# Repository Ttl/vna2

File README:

Second version of the homemade 30 MHZ - 6 GHz single receiver VNA design files.

First version: https://github.com/Ttl/vna

For more information see: http://hforsten.com/improved-homemade-vna.html

FPGA can be programmed with Openocd (http://openocd.org/). Scripts for programming the FPGA and SPI flash are in the "openocd" folder. Copy the bit file to openocd folder and use the command "openocd -f <script.cfg>" to program the board.

Before communication is possible with the board through USB, FT2232D EEPROM needs to be programmed. Port B needs to be changed in FIFO 245 mode. This can be done using FTDIs "ft-prog" tool.

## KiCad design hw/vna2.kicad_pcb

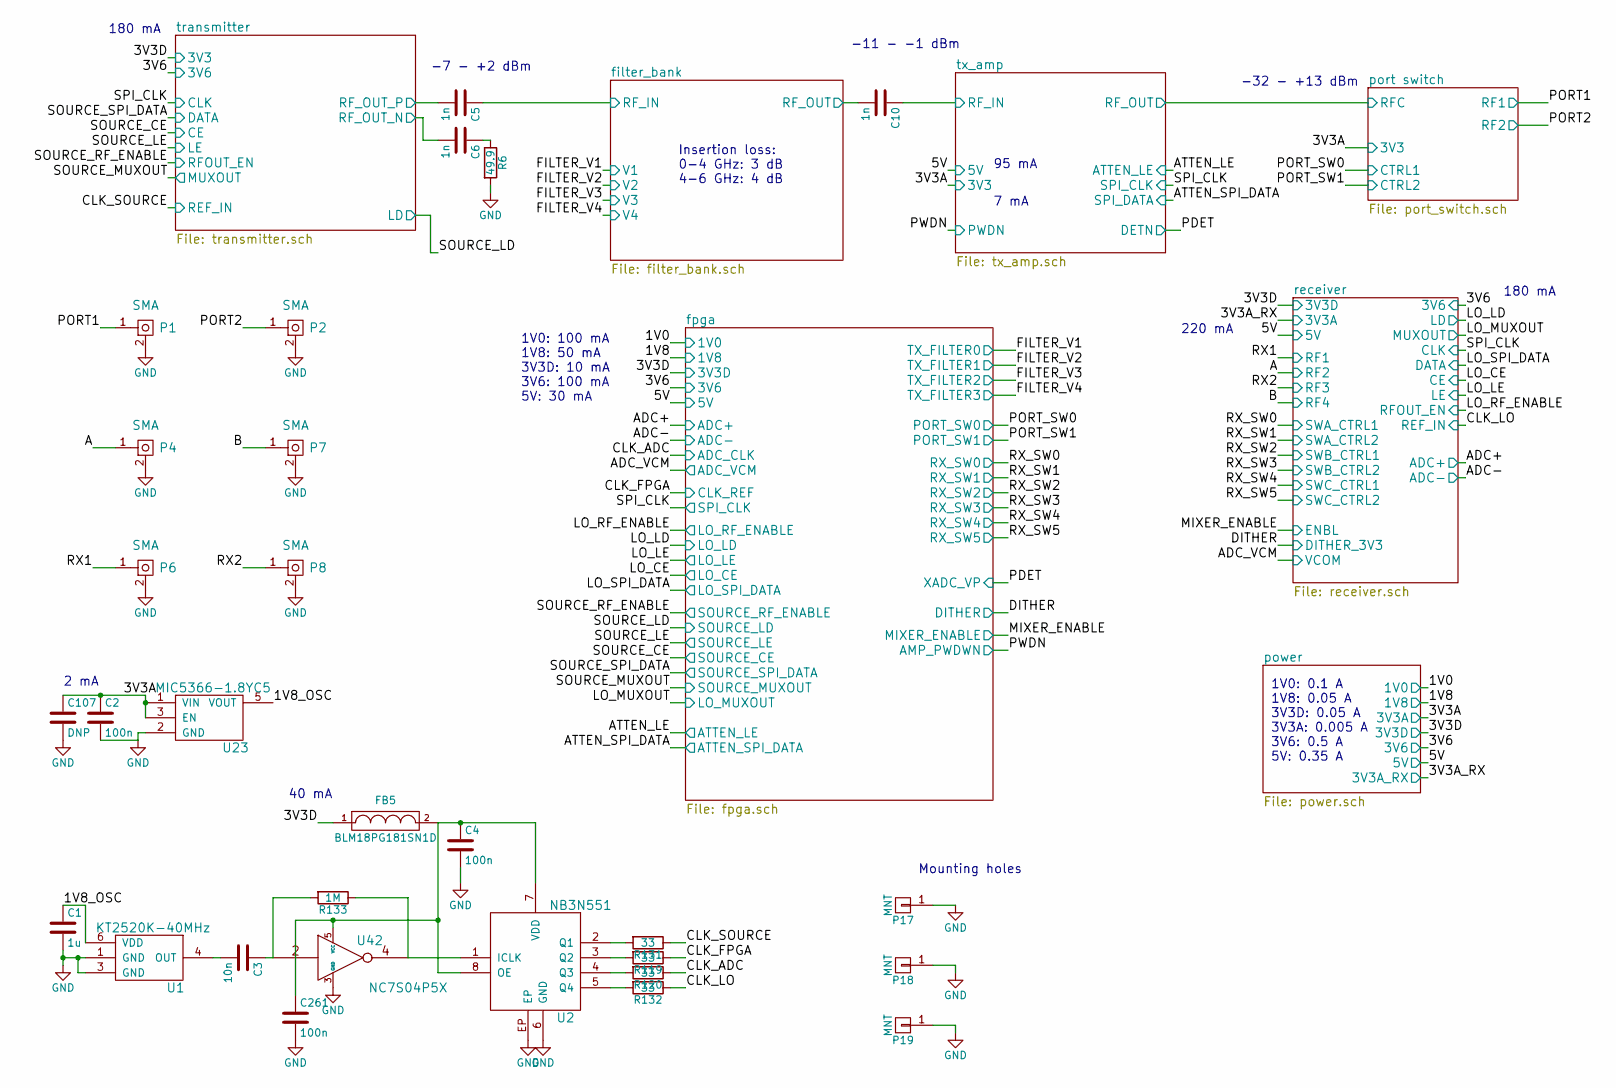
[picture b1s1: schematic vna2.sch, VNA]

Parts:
C1: 1u; C_0402b
C2, C4, C261: 100n; C_0402b
C3: 10n; C_0402b
C5, C6, C10: 1n; C_0402b
C107: DNP; C_0805b
FB5: BLM18PG181SN1D; C_0603b
P1, P2, P4, P6, P7, P8: SMA; CONSMA003.062
P17, P18, P19: MNT; MountingHole_3.2mm_M3_Pad_Via_mod
R6: 49.9; R_0402b
R119, R120, R131, R132: 33; R_0402b
R133: 1M; R_0402b
U1: KT2520K-40MHz; KT2520K
U2: NB3N551; DFN-8
U23: MIC5366-1.8YC5; SOT-353
U42: NC7S04P5X; SOT-353

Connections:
/1V8_OSC: C1.1, U1.6 (VDD), U23.5 (VOUT)
/3V3A: C2.1, C107.1, U23.1 (VIN), U23.3 (EN); also elsewhere on the board
/3V3D: FB5.1; also elsewhere on the board
/A: P4.1; also elsewhere on the board
/B: P7.1; also elsewhere on the board
/CLK_ADC: R120.1; also elsewhere on the board
/CLK_FPGA: R119.1; also elsewhere on the board
/CLK_LO: R132.1; also elsewhere on the board
/CLK_SOURCE: R131.1; also elsewhere on the board
/PORT1: P1.1; also elsewhere on the board
/PORT2: P2.1; also elsewhere on the board
/RX1: P6.1; also elsewhere on the board
/RX2: P8.1; also elsewhere on the board
/filter_bank/RF_IN: C5.1; also elsewhere on the board
/filter_bank/RF_OUT: C10.2; also elsewhere on the board
/transmitter/RF_OUT_N: C6.2; also elsewhere on the board
/transmitter/RF_OUT_P: C5.2; also elsewhere on the board
/tx_amp/RF_IN: C10.1; also elsewhere on the board
GND: C1.2, C2.2, C4.2, C107.2, C261.2, P1.2, P2.2, P4.2, P6.2, P7.2, P8.2, P17.1, P18.1, P19.1, R6.2, U1.1 (GND), U1.3 (GND), U2.6 (GND), U2.EP, U23.2 (GND), U42.3 (GND); also elsewhere on the board
unnamed: C3.1, R133.2, U42.2
unnamed: C3.2, U1.4 (OUT)
unnamed: C6.1, R6.1
unnamed: C4.1, C261.1, FB5.2, U2.7 (VDD), U2.8 (OE), U42.5 (VCC)
unnamed: R119.2, U2.3 (Q2)
unnamed: R120.2, U2.4 (Q3)
unnamed: R131.2, U2.2 (Q1)
unnamed: R132.2, U2.5 (Q4)
unnamed: R133.1, U2.1 (ICLK), U42.4

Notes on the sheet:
2 mA
Insertion loss: 0-4 GHz: 3 dB 4-6 GHz: 4 dB
-7 - +2 dBm
-11 - -1 dBm
-32 - +13 dBm
180 mA
220 mA
95 mA
7 mA
1V0: 100 mA 1V8: 50 mA 3V3D: 10 mA 3V6: 100 mA 5V: 30 mA
1V0: 0.1 A 1V8: 0.05 A 3V3D: 0.05 A 3V3A: 0.005 A 3V6: 0.5 A 5V: 0.35 A
Mounting holes
40 mA

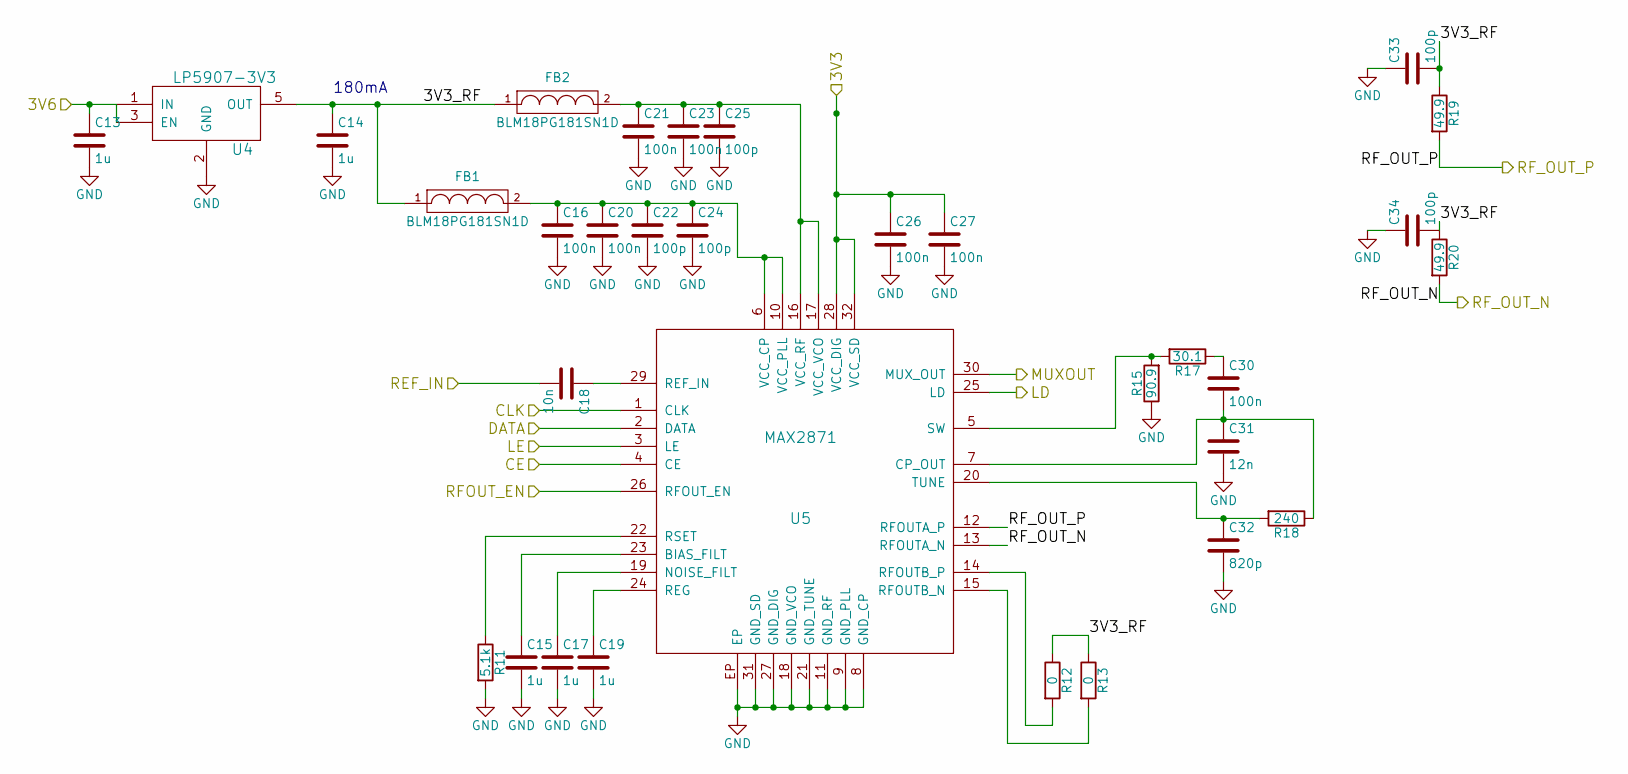
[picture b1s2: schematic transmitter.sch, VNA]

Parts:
C13, C14, C15, C17, C19: 1u; C_0603b
C16, C20, C21, C23, C26, C27, C30: 100n; C_0402b
C18: 10n; C_0402b
C22, C24, C25, C33, C34: 100p; C_0402b
C31: 12n; C_0402b
C32: 820p; C_0402b
FB1, FB2: BLM18PG181SN1D; C_0603b
R11: 5.1k; R_0402b
R12, R13: 0; R_0402b
R15: 90.9; R_0402b
R17: 30.1; R_0402b
R18: 240; R_0402b
R19, R20: 49.9; R_0402b
U4: LP5907-3V3; SOT-23-5
U5: MAX2871; TQFN-32

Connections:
/3V3D: C26.1, C27.1, U5.28 (VCC_DIG), U5.32 (VCC_SD); also elsewhere on the board
/3V6: C13.1, U4.1 (IN), U4.3 (EN); also elsewhere on the board
/CLK_SOURCE: C18.2; also elsewhere on the board
/SOURCE_CE: U5.4 (CE); also elsewhere on the board
/SOURCE_LD: U5.25 (LD); also elsewhere on the board
/SOURCE_LE: U5.3 (LE); also elsewhere on the board
/SOURCE_MUXOUT: U5.30 (MUX_OUT); also elsewhere on the board
/SOURCE_RF_ENABLE: U5.26 (RFOUT_EN); also elsewhere on the board
/SOURCE_SPI_DATA: U5.2 (DATA); also elsewhere on the board
/SPI_CLK: U5.1 (CLK); also elsewhere on the board
/transmitter/3V3_RF: C14.1, C33.2, C34.2, FB1.1, FB2.1, R12.1, R13.1, R19.1, R20.1, U4.5 (OUT)
/transmitter/RF_OUT_N: R20.2, U5.13 (RFOUTA_N); also elsewhere on the board
/transmitter/RF_OUT_P: R19.2, U5.12 (RFOUTA_P); also elsewhere on the board
GND: C13.2, C14.2, C15.2, C16.2, C17.2, C19.2, C20.2, C21.2, C22.2, C23.2, C24.2, C25.2, C26.2, C27.2, C31.2, C32.2, C33.1, C34.1, R11.2, R15.1, U4.2 (GND), U5.8 (GND_CP), U5.9 (GND_PLL), U5.11 (GND_RF), U5.18 (GND_VCO), U5.21 (GND_TUNE), U5.27 (GND_DIG), U5.31 (GND_SD), U5.EP; also elsewhere on the board
unnamed: C15.1, U5.23 (BIAS_FILT)
unnamed: C16.1, C20.1, C22.1, C24.1, FB1.2, U5.6 (VCC_CP), U5.10 (VCC_PLL)
unnamed: C17.1, U5.19 (NOISE_FILT)
unnamed: C18.1, U5.29 (REF_IN)
unnamed: C19.1, U5.24 (REG)
unnamed: C21.1, C23.1, C25.1, FB2.2, U5.16 (VCC_RF), U5.17 (VCC_VCO)
unnamed: C30.1, R17.1
unnamed: C30.2, C31.1, R18.1, U5.7 (CP_OUT)
unnamed: C32.1, R18.2, U5.20 (TUNE)
unnamed: R11.1, U5.22 (RSET)
unnamed: R12.2, U5.14 (RFOUTB_P)
unnamed: R13.2, U5.15 (RFOUTB_N)
unnamed: R15.2, R17.2, U5.5 (SW)

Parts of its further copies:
C55, C56, C57, C59, C61: 1u; C_0603b
C58, C62, C63, C65, C68, C69, C72: 100n; C_0402b
C60: 10n; C_0402b
C64, C66, C67, C75, C76: 100p; C_0402b
C73: 12n; C_0402b
C74: 820p; C_0402b
FB3, FB4: BLM18PG181SN1D; C_0603b
R29: 5.1k; R_0402b
R30, R31: 0; R_0402b
R33: 90.9; R_0402b
R35: 30.1; R_0402b
R36: 240; R_0402b
R37, R38: 49.9; R_0402b
U8: LP5907-3V3; SOT-23-5
U9: MAX2871; TQFN-32

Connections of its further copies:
/3V3D: C68.1, C69.1, U9.28 (VCC_DIG), U9.32 (VCC_SD); also elsewhere on the board
/3V6: C55.1, U8.1 (IN), U8.3 (EN); also elsewhere on the board
/CLK_LO: C60.2; also elsewhere on the board
/LO_CE: U9.4 (CE); also elsewhere on the board
/LO_LD: U9.25 (LD); also elsewhere on the board
/LO_LE: U9.3 (LE); also elsewhere on the board
/LO_MUXOUT: U9.30 (MUX_OUT); also elsewhere on the board
/LO_RF_ENABLE: U9.26 (RFOUT_EN); also elsewhere on the board
/LO_SPI_DATA: U9.2 (DATA); also elsewhere on the board
/SPI_CLK: U9.1 (CLK); also elsewhere on the board
/receiver/LON: R38.2, U9.13 (RFOUTA_N); also elsewhere on the board
/receiver/LOP: R37.2, U9.12 (RFOUTA_P); also elsewhere on the board
/receiver/lo_synth/3V3_RF: C56.1, C75.2, C76.2, FB3.1, FB4.1, R30.1, R31.1, R37.1, R38.1, U8.5 (OUT)
GND: C55.2, C56.2, C57.2, C58.2, C59.2, C61.2, C62.2, C63.2, C64.2, C65.2, C66.2, C67.2, C68.2, C69.2, C73.2, C74.2, C75.1, C76.1, R29.2, R33.1, U8.2 (GND), U9.8 (GND_CP), U9.9 (GND_PLL), U9.11 (GND_RF), U9.18 (GND_VCO), U9.21 (GND_TUNE), U9.27 (GND_DIG), U9.31 (GND_SD), U9.EP; also elsewhere on the board
unnamed: C57.1, U9.23 (BIAS_FILT)
unnamed: C58.1, C62.1, C64.1, C66.1, FB3.2, U9.6 (VCC_CP), U9.10 (VCC_PLL)
unnamed: C59.1, U9.19 (NOISE_FILT)
unnamed: C60.1, U9.29 (REF_IN)
unnamed: C61.1, U9.24 (REG)
unnamed: C63.1, C65.1, C67.1, FB4.2, U9.16 (VCC_RF), U9.17 (VCC_VCO)
unnamed: C72.1, R35.1
unnamed: C72.2, C73.1, R36.1, U9.7 (CP_OUT)
unnamed: C74.1, R36.2, U9.20 (TUNE)
unnamed: R29.1, U9.22 (RSET)
unnamed: R30.2, U9.14 (RFOUTB_P)
unnamed: R31.2, U9.15 (RFOUTB_N)
unnamed: R33.2, R35.2, U9.5 (SW)

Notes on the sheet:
180mA

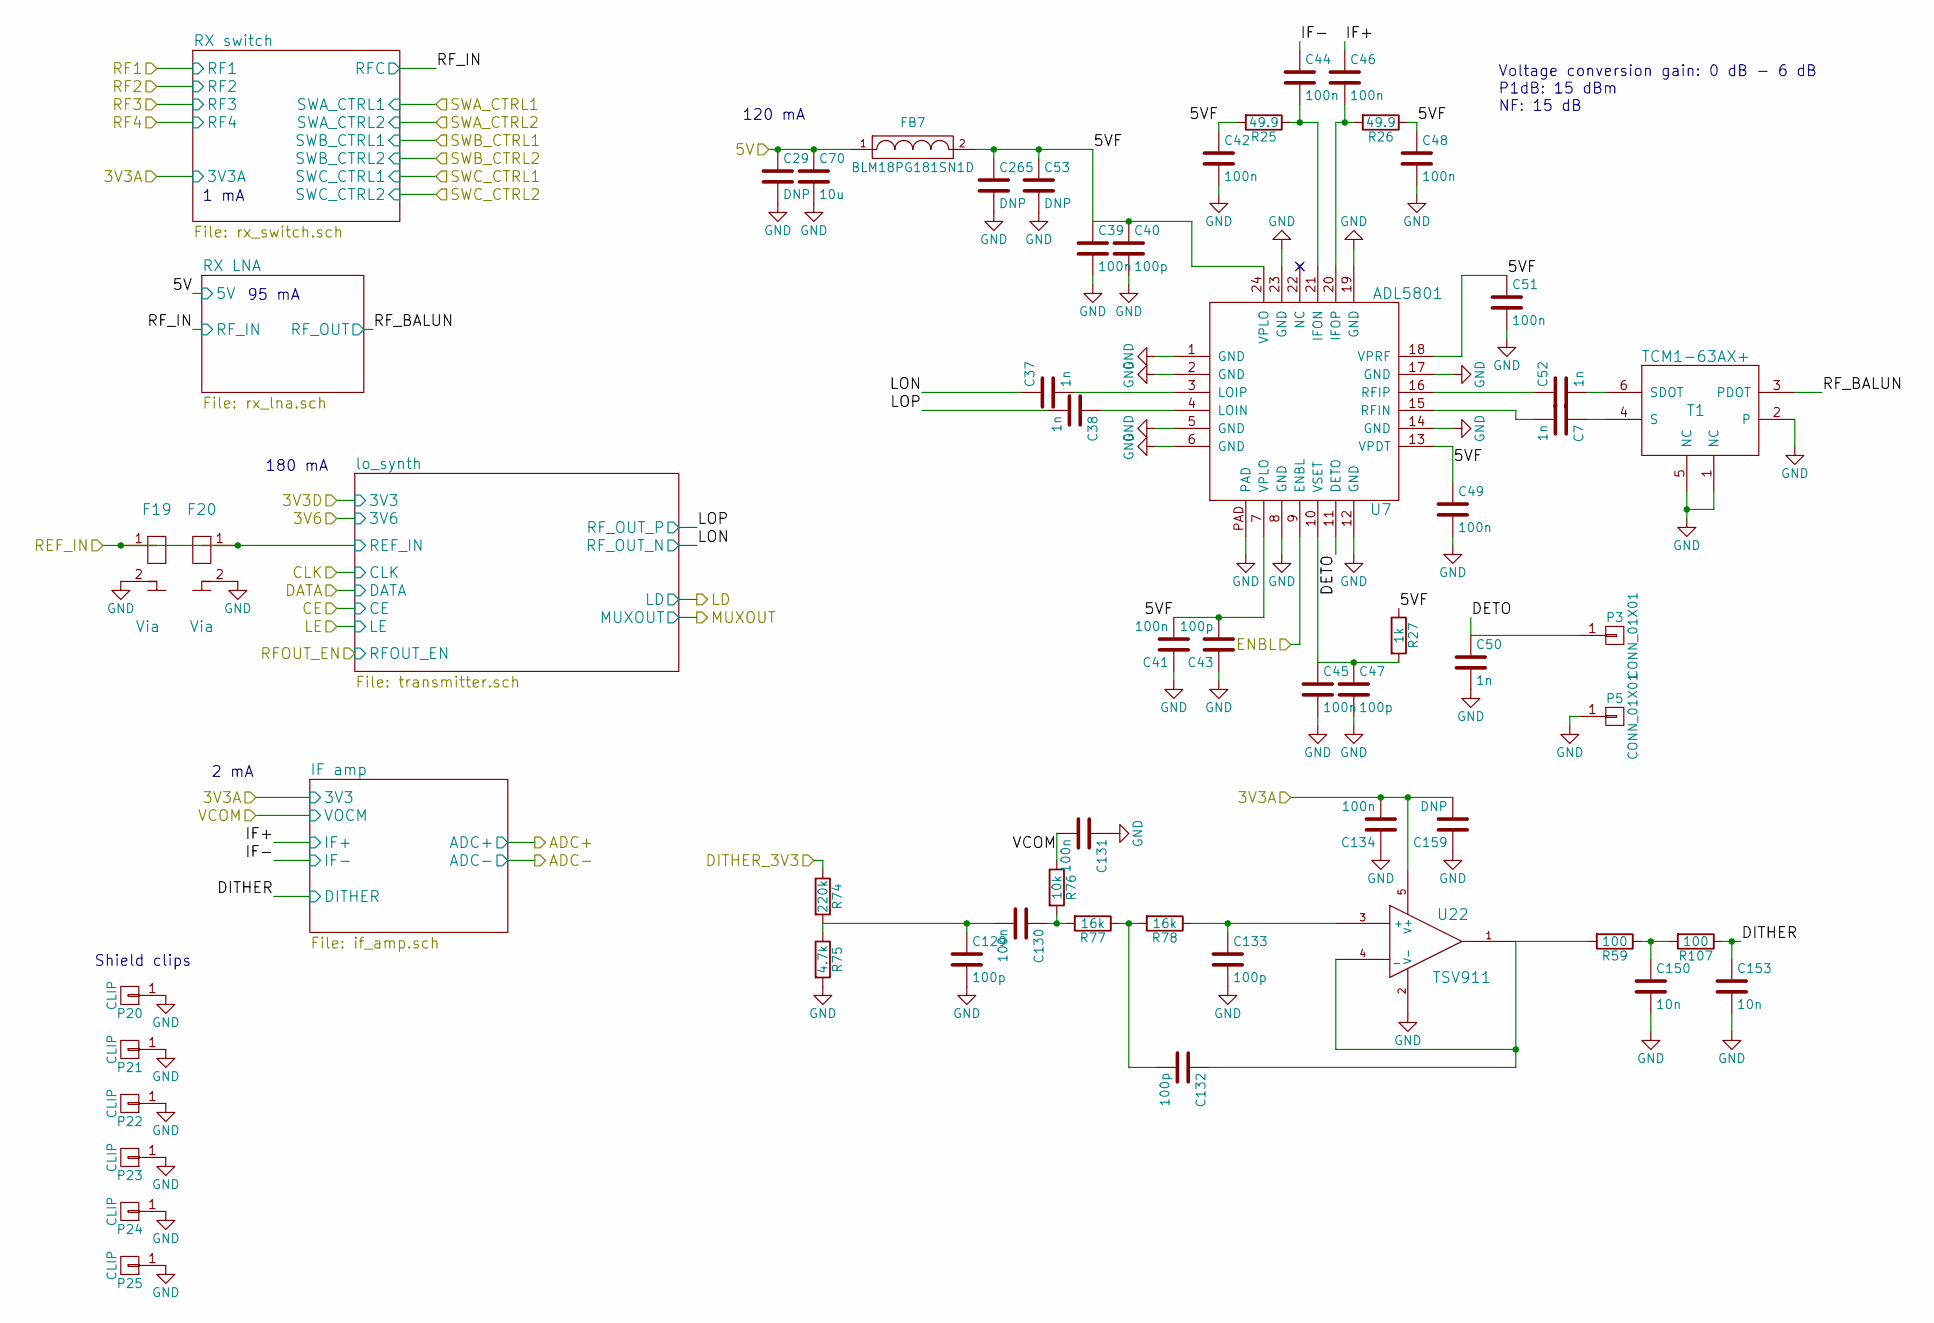
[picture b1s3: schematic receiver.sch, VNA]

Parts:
C7, C37, C38, C50, C52: 1n; C_0402b
C29: DNP; C_0603b
C39, C41, C42, C44, C45, C46, C48, C49, C51, C130, C131, C134: 100n; C_0402b
C40, C43, C47, C129, C132, C133: 100p; C_0402b
C53, C159, C265: DNP; C_0805b
C70: 10u; C_0805b
C150, C153: 10n; C_0402b
F19, F20: Via; RF_via
FB7: BLM18PG181SN1D; C_0603b
P3, P5: CONN_01X01; TP_1.00
P20, P21, P22, P23, P24, P25: CLIP; S2711-46R
R25, R26: 49.9; R_0402b
R27: 1k; R_0402b
R59, R107: 100; R_0402b
R74: 220k; R_0402b
R75: 4.7k; R_0402b
R76: 10k; R_0402b
R77, R78: 16k; R_0402b
T1: TCM1-63AX+
U7: ADL5801; VFQFN-24
U22: TSV911; SOT-23-5

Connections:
3V3A_RX: C134.2, C159.2, U22.5 (V+); also elsewhere on the board
/5V: C29.1, C70.1, FB7.1; also elsewhere on the board
/ADC_VCM: C131.2, R76.1; also elsewhere on the board
/CLK_LO: F19.1, F20.1; also elsewhere on the board
/DITHER: R74.1; also elsewhere on the board
/MIXER_ENABLE: U7.9 (ENBL); also elsewhere on the board
/receiver/5VF: C39.1, C40.1, C41.2, C42.1, C43.2, C48.1, C49.1, C51.1, C53.1, C265.1, FB7.2, R25.2, R26.1, R27.1, U7.7 (VPLO), U7.13 (VPDT), U7.18 (VPRF), U7.24 (VPLO)
/receiver/DETO: C50.1, P3.1, U7.11 (DETO)
/receiver/DITHER: C153.1, R107.1; also elsewhere on the board
/receiver/IF+: C46.1; also elsewhere on the board
/receiver/IF-: C44.1; also elsewhere on the board
/receiver/LON: C37.1; also elsewhere on the board
/receiver/LOP: C38.2; also elsewhere on the board
/receiver/RF_BALUN: T1.3 (PDOT); also elsewhere on the board
GND: C29.2, C39.2, C40.2, C41.1, C42.2, C43.1, C45.2, C47.2, C48.2, C49.2, C50.2, C51.2, C53.2, C70.2, C129.2, C131.1, C133.2, C134.1, C150.2, C153.2, C159.1, C265.2, F19.2, F20.2, P5.1, P20.1, P21.1, P22.1, P23.1, P24.1, P25.1, R75.2, T1.1 (NC), T1.2, T1.5 (NC), U7.1 (GND), U7.2 (GND), U7.5 (GND), U7.6 (GND), U7.8 (GND), U7.12 (GND), U7.14 (GND), U7.17 (GND), U7.19 (GND), U7.23 (GND), U7.PAD, U22.2 (V-); also elsewhere on the board
unnamed: C7.1, T1.4 (S)
unnamed: C7.2, U7.15 (RFIN)
unnamed: C37.2, U7.3 (LOIP)
unnamed: C38.1, U7.4 (LOIN)
unnamed: C44.2, R25.1, U7.21 (IFON)
unnamed: C45.1, C47.1, R27.2, U7.10 (VSET)
unnamed: C46.2, R26.2, U7.20 (IFOP)
unnamed: C52.1, U7.16 (RFIP)
unnamed: C52.2, T1.6 (SDOT)
unnamed: C129.1, C130.2, R74.2, R75.1
unnamed: C130.1, R76.2, R77.2
unnamed: C132.1, R59.2, U22.1, U22.4 (_)
unnamed: C132.2, R77.1, R78.2
unnamed: C133.1, R78.1, U22.3 (+)
unnamed: C150.1, R59.1, R107.2

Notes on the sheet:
Voltage conversion gain: 0 dB - 6 dB P1dB: 15 dBm NF: 15 dB
120 mA
180 mA
2 mA
Shield clips
1 mA
95 mA

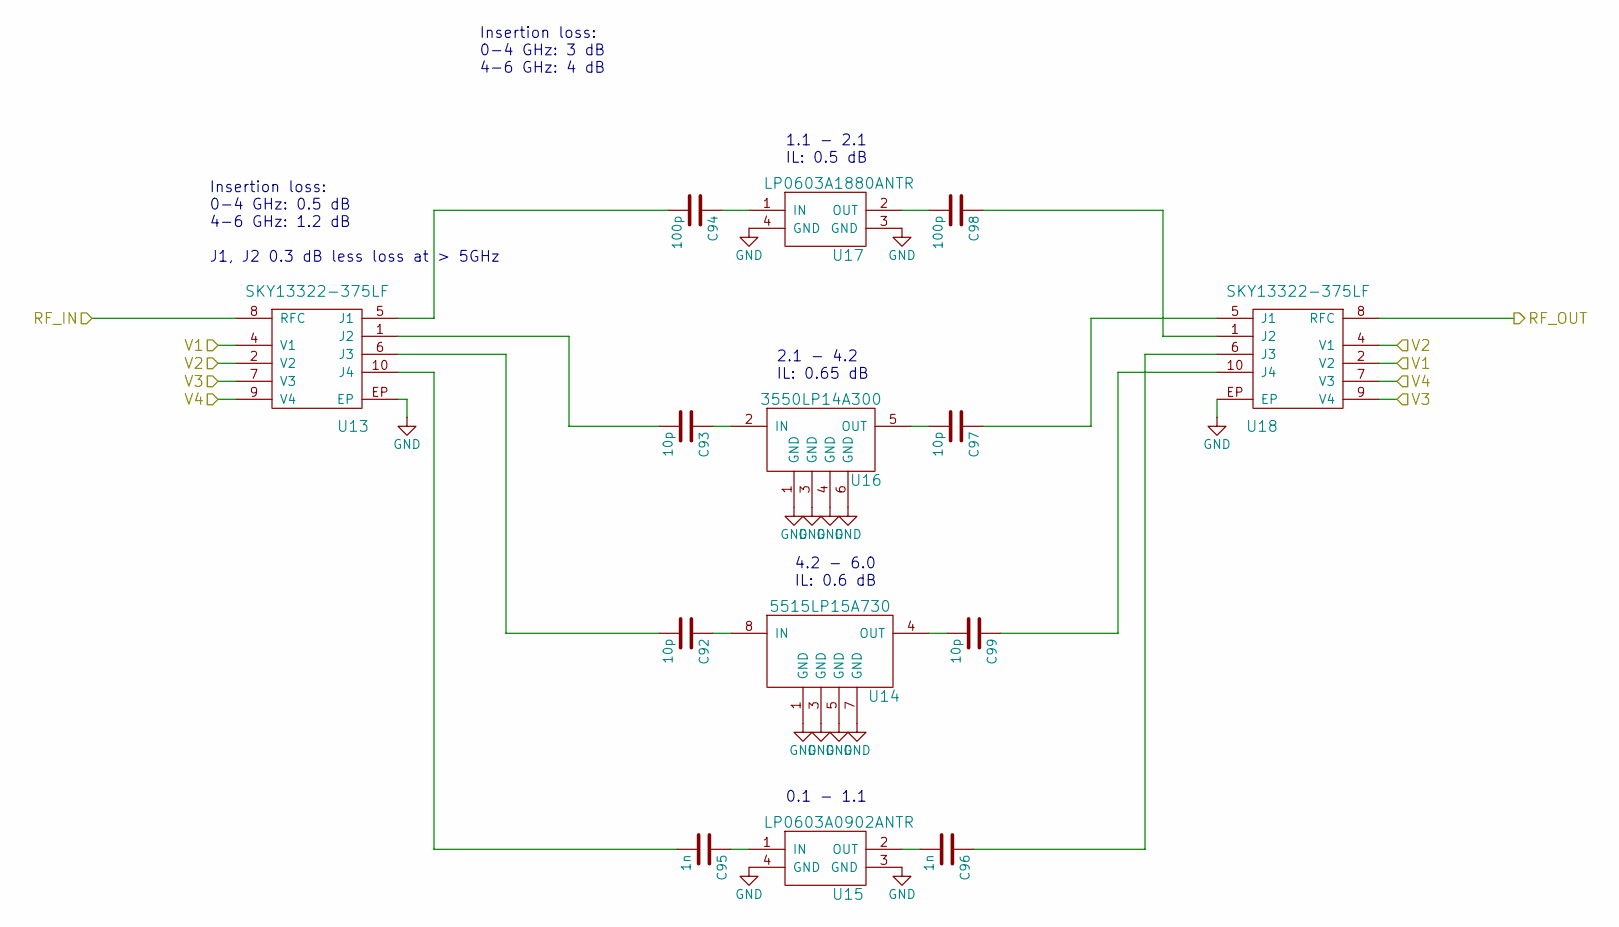
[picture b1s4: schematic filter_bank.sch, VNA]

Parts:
C92, C93, C97, C99: 10p; C_0402b
C94, C98: 100p; C_0402b
C95, C96: 1n; C_0402b
U13, U18: SKY13322-375LF; MLPD-10
U14: 5515LP15A730
U15: LP0603A0902ANTR; LP0603A0902
U16: 3550LP14A300
U17: LP0603A1880ANTR; LP0603A0902

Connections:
/FILTER_V1: U13.4 (V1), U18.2 (V2); also elsewhere on the board
/FILTER_V2: U13.2 (V2), U18.4 (V1); also elsewhere on the board
/FILTER_V3: U13.7 (V3), U18.9 (V4); also elsewhere on the board
/FILTER_V4: U13.9 (V4), U18.7 (V3); also elsewhere on the board
/filter_bank/RF_IN: U13.8 (RFC); also elsewhere on the board
/filter_bank/RF_OUT: U18.8 (RFC); also elsewhere on the board
GND: U13.EP, U14.1 (GND), U14.3 (GND), U14.5 (GND), U14.7 (GND), U15.3 (GND), U15.4 (GND), U16.1 (GND), U16.3 (GND), U16.4 (GND), U16.6 (GND), U17.3 (GND), U17.4 (GND), U18.EP; also elsewhere on the board
unnamed: C92.1, U14.8 (IN)
unnamed: C92.2, U13.6 (J3)
unnamed: C93.1, U16.2 (IN)
unnamed: C93.2, U13.1 (J2)
unnamed: C94.1, U17.1 (IN)
unnamed: C94.2, U13.5 (J1)
unnamed: C95.1, U15.1 (IN)
unnamed: C95.2, U13.10 (J4)
unnamed: C96.1, U18.6 (J3)
unnamed: C96.2, U15.2 (OUT)
unnamed: C97.1, U18.5 (J1)
unnamed: C97.2, U16.5 (OUT)
unnamed: C98.1, U18.1 (J2)
unnamed: C98.2, U17.2 (OUT)
unnamed: C99.1, U18.10 (J4)
unnamed: C99.2, U14.4 (OUT)

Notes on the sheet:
Insertion loss: 0-4 GHz: 0.5 dB 4-6 GHz: 1.2 dB J1, J2 0.3 dB less loss at > 5GHz
Insertion loss: 0-4 GHz: 3 dB 4-6 GHz: 4 dB
4.2 - 6.0 IL: 0.6 dB
2.1 - 4.2 IL: 0.65 dB
1.1 - 2.1 IL: 0.5 dB
0.1 - 1.1

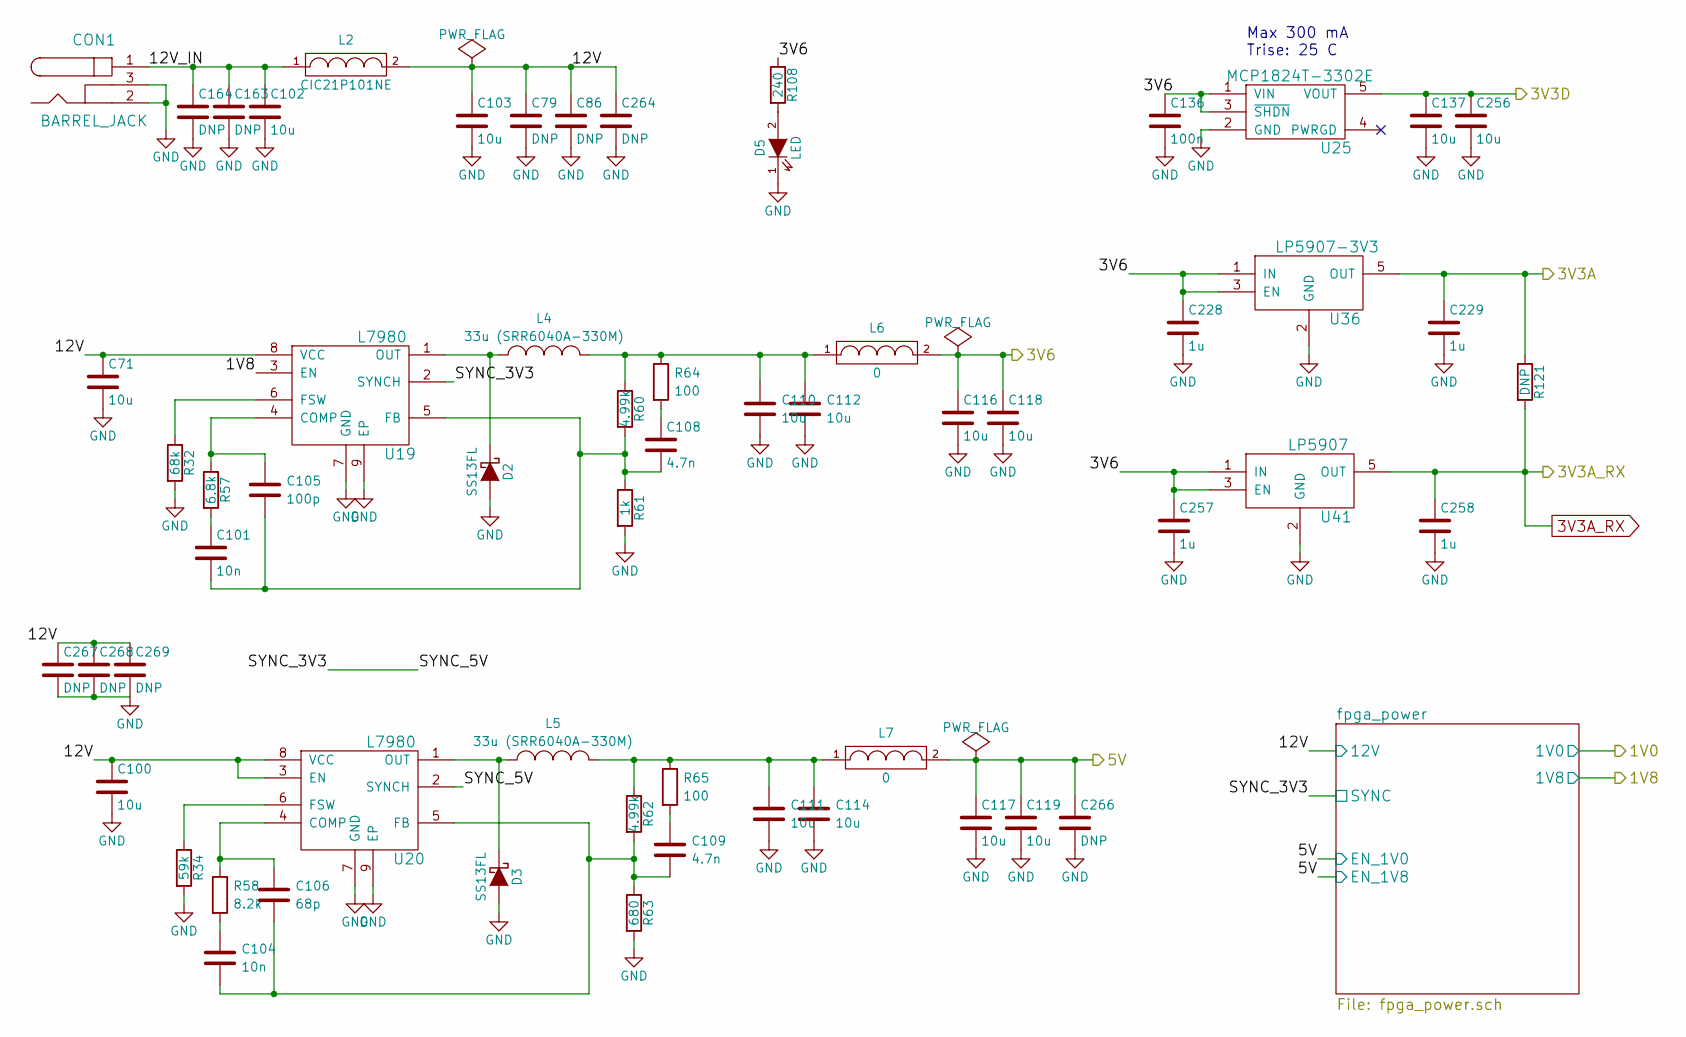
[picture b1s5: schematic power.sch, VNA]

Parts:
C71, C100, C102, C103, C110, C111, C112, C114, C116, C117, C118, C119, C137, C256: 10u; C_0805b
C79, C86, C163, C164, C264, C266, C267, C268, C269: DNP; C_0805b
C101, C104: 10n; C_0402b
C105: 100p; C_0402b
C106: 68p; C_0402b
C108, C109: 4.7n; C_0402b
C136: 100n; C_0402b
C228, C229, C257, C258: 1u; C_0603b
CON1: BARREL_JACK; EJ508A
D2, D3: SS13FL; SOD-123F
D5: LED; LED_0603
L2: CIC21P101NE; C_0805b
L4, L5: 33u (SRR6040A-330M); SRR6040A
L6, L7: 0; C_0805b
R32: 68k; R_0402b
R34: 59k; R_0402b
R57: 6.8k; R_0402b
R58: 8.2k; R_0402b
R60, R62: 4.99k; R_0402b
R61: 1k; R_0402b
R63: 680; R_0402b
R64, R65: 100; R_0402b
R108: 240; R_0402b
R121: DNP; R_0402b
U19, U20: L7980; DFN-8-1EP_3x3mm_Pitch0.5mm
U25: MCP1824T-3302E; SOT-23-5
U36: LP5907-3V3; SOT-23-5
U41: LP5907; SOT-23-5

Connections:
3V3A_RX: C258.1, R121.2, U41.5 (OUT); also elsewhere on the board
/1V8: U19.3 (EN); also elsewhere on the board
/3V3A: C229.1, R121.1, U36.5 (OUT); also elsewhere on the board
/3V3D: C137.1, C256.1, U25.5 (VOUT); also elsewhere on the board
/3V6: C116.1, C118.1, C136.1, C228.1, C257.1, L6.2, R108.1, U25.1 (VIN), U25.3 (~SHDN), U36.1 (IN), U36.3 (EN), U41.1 (IN), U41.3 (EN); also elsewhere on the board
/5V: C117.1, C119.1, C266.1, L7.2; also elsewhere on the board
/power/12V: C71.1, C79.1, C86.1, C100.1, C103.1, C264.1, C267.1, C268.1, C269.1, L2.2, U19.8 (VCC), U20.3 (EN), U20.8 (VCC); also elsewhere on the board
/power/12V_IN: C102.1, C163.1, C164.1, CON1.1, L2.1
/power/SYNC_3V3: U19.2 (SYNCH), U20.2 (SYNCH); also elsewhere on the board
GND: C71.2, C79.2, C86.2, C100.2, C102.2, C103.2, C110.2, C111.2, C112.2, C114.2, C116.2, C117.2, C118.2, C119.2, C136.2, C137.2, C163.2, C164.2, C228.2, C229.2, C256.2, C257.2, C258.2, C264.2, C266.2, C267.2, C268.2, C269.2, CON1.2, CON1.3, D2.2 (A), D3.2 (A), D5.1 (K), R32.2, R34.2, R61.2, R63.2, U19.7 (GND), U19.9 (EP), U20.7 (GND), U20.9 (EP), U25.2 (GND), U36.2 (GND), U41.2 (GND); also elsewhere on the board
unnamed: C101.1, R57.2
unnamed: C101.2, C105.2, C108.2, R60.2, R61.1, U19.5 (FB)
unnamed: C104.1, R58.2
unnamed: C104.2, C106.2, C109.2, R62.2, R63.1, U20.5 (FB)
unnamed: C105.1, R57.1, U19.4 (COMP)
unnamed: C106.1, R58.1, U20.4 (COMP)
unnamed: C108.1, R64.2
unnamed: C109.1, R65.2
unnamed: C110.1, C112.1, L4.2, L6.1, R60.1, R64.1
unnamed: C111.1, C114.1, L5.2, L7.1, R62.1, R65.1
unnamed: D2.1 (K), L4.1, U19.1 (OUT)
unnamed: D3.1 (K), L5.1, U20.1 (OUT)
unnamed: D5.2 (A), R108.2
unnamed: R32.1, U19.6 (FSW)
unnamed: R34.1, U20.6 (FSW)

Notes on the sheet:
Max 300 mA Trise: 25 C

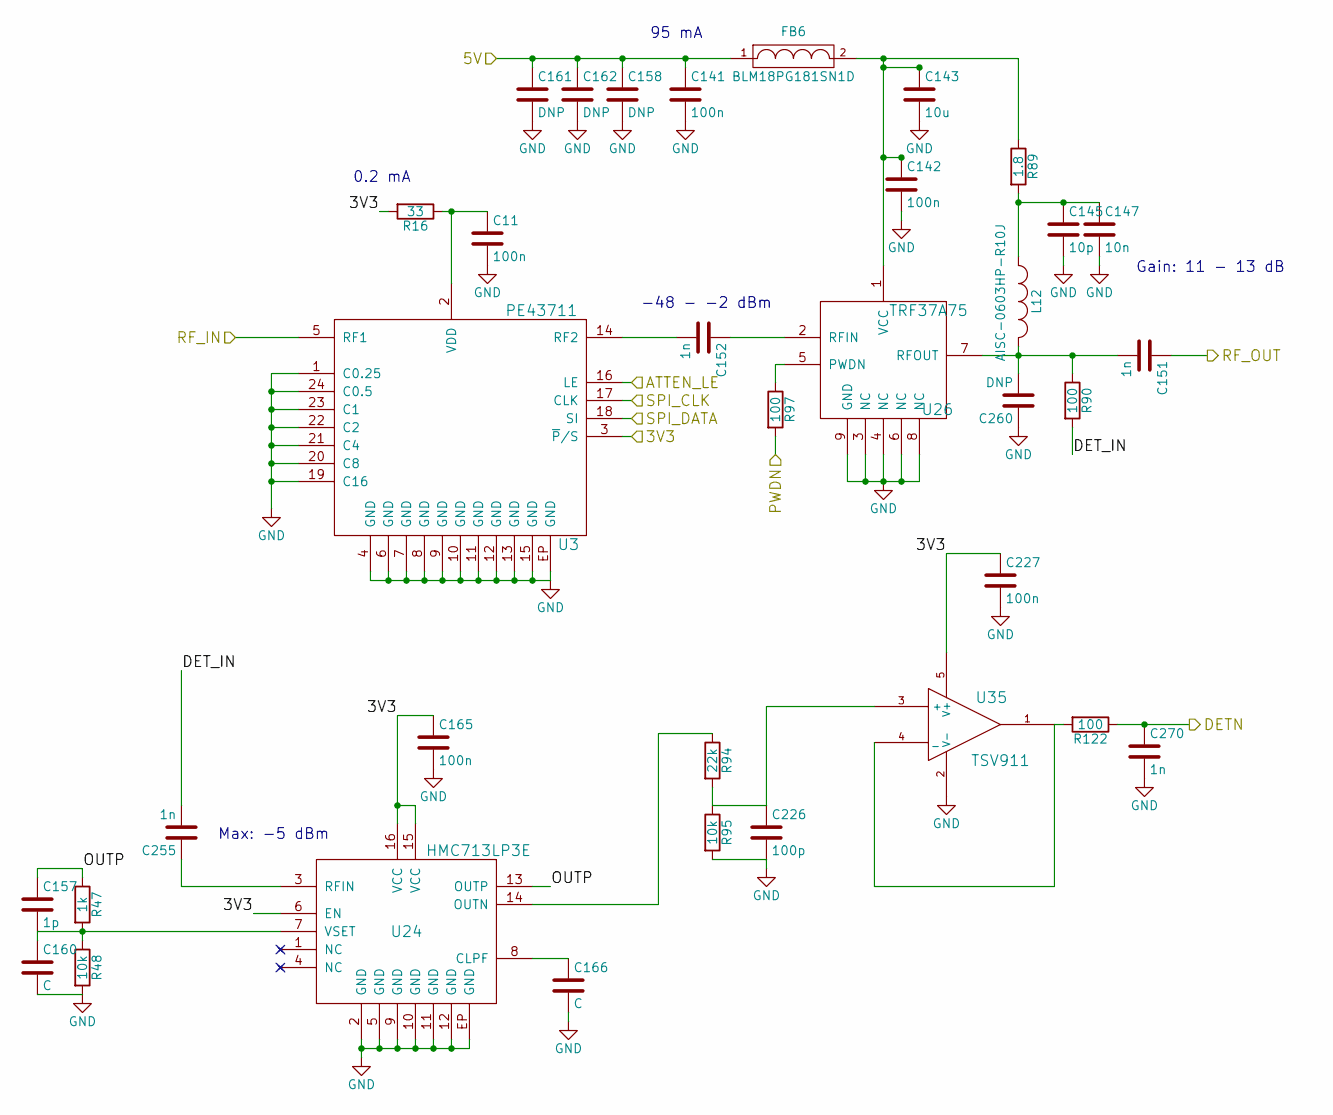
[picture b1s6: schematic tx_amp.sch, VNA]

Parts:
C11, C141, C142, C165, C227: 100n; C_0402b
C143: 10u; C_0805b
C145: 10p; C_0402b
C147: 10n; C_0402b
C151, C152, C255, C270: 1n; C_0402b
C157: 1p; C_0402b
C158: DNP; C_0805b
C160, C166: C; C_0402b
C161, C162, C260: DNP; C_0402b
C226: 100p; C_0402b
FB6: BLM18PG181SN1D; C_0603b
L12: AISC-0603HP-R10J; C_0603b
R16: 33; R_0402b
R47: 1k; R_0402b
R48, R95: 10k; R_0402b
R89: 1.8; R_0603b
R90, R97, R122: 100; R_0402b
R94: 22k; R_0402b
U3: PE43711; VQFN-24
U24: HMC713LP3E; VFQFN-16
U26: TRF37A75; DFN-8-1EP_2x2mm_Pitch0.5mm
U35: TSV911; SOT-23-5

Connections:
/3V3A: C165.1, C227.1, R16.2, U3.3 (~P~/S), U24.6 (EN), U24.15 (VCC), U24.16 (VCC), U35.5 (V+); also elsewhere on the board
/5V: C141.1, C158.1, C161.1, C162.1, FB6.1; also elsewhere on the board
/ATTEN_LE: U3.16 (LE); also elsewhere on the board
/ATTEN_SPI_DATA: U3.18 (SI); also elsewhere on the board
/PDET: C270.1, R122.1; also elsewhere on the board
/PWDN: R97.2; also elsewhere on the board
/SPI_CLK: U3.17 (CLK); also elsewhere on the board
/port switch/RFC: C151.1; also elsewhere on the board
/tx_amp/DET_IN: C255.2, R90.2
/tx_amp/OUTP: C157.1, R47.1, U24.13 (OUTP)
/tx_amp/RF_IN: U3.5 (RF1); also elsewhere on the board
GND: C11.2, C141.2, C142.2, C143.2, C145.2, C147.2, C158.2, C160.2, C161.2, C162.2, C165.2, C166.2, C226.2, C227.2, C260.1, C270.2, R48.2, R95.2, U3.1 (C0.25), U3.4 (GND), U3.6 (GND), U3.7 (GND), U3.8 (GND), U3.9 (GND), U3.10 (GND), U3.11 (GND), U3.12 (GND), U3.13 (GND), U3.15 (GND), U3.19 (C16), U3.20 (C8), U3.21 (C4), U3.22 (C2), U3.23 (C1), U3.24 (C0.5), U3.EP (GND), U24.2 (GND), U24.5 (GND), U24.9 (GND), U24.10 (GND), U24.11 (GND), U24.12 (GND), U24.EP (GND), U26.3 (NC), U26.4 (NC), U26.6 (NC), U26.8 (NC), U26.9 (GND), U35.2 (V-); also elsewhere on the board
unnamed: C11.1, R16.1, U3.2 (VDD)
unnamed: C142.1, C143.1, FB6.2, R89.1, U26.1 (VCC)
unnamed: C145.1, C147.1, L12.1, R89.2
unnamed: C151.2, C260.2, L12.2, R90.1, U26.7 (RFOUT)
unnamed: C152.1, U26.2 (RFIN)
unnamed: C152.2, U3.14 (RF2)
unnamed: C157.2, C160.1, R47.2, R48.1, U24.7 (VSET)
unnamed: C166.1, U24.8 (CLPF)
unnamed: C226.1, R94.2, R95.1, U35.3 (+)
unnamed: C255.1, U24.3 (RFIN)
unnamed: R94.1, U24.14 (OUTN)
unnamed: R97.1, U26.5 (PWDN)
unnamed: R122.2, U35.1, U35.4 (_)

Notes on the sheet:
-48 - -2 dBm
Gain: 11 - 13 dB
95 mA
0.2 mA
Max: -5 dBm

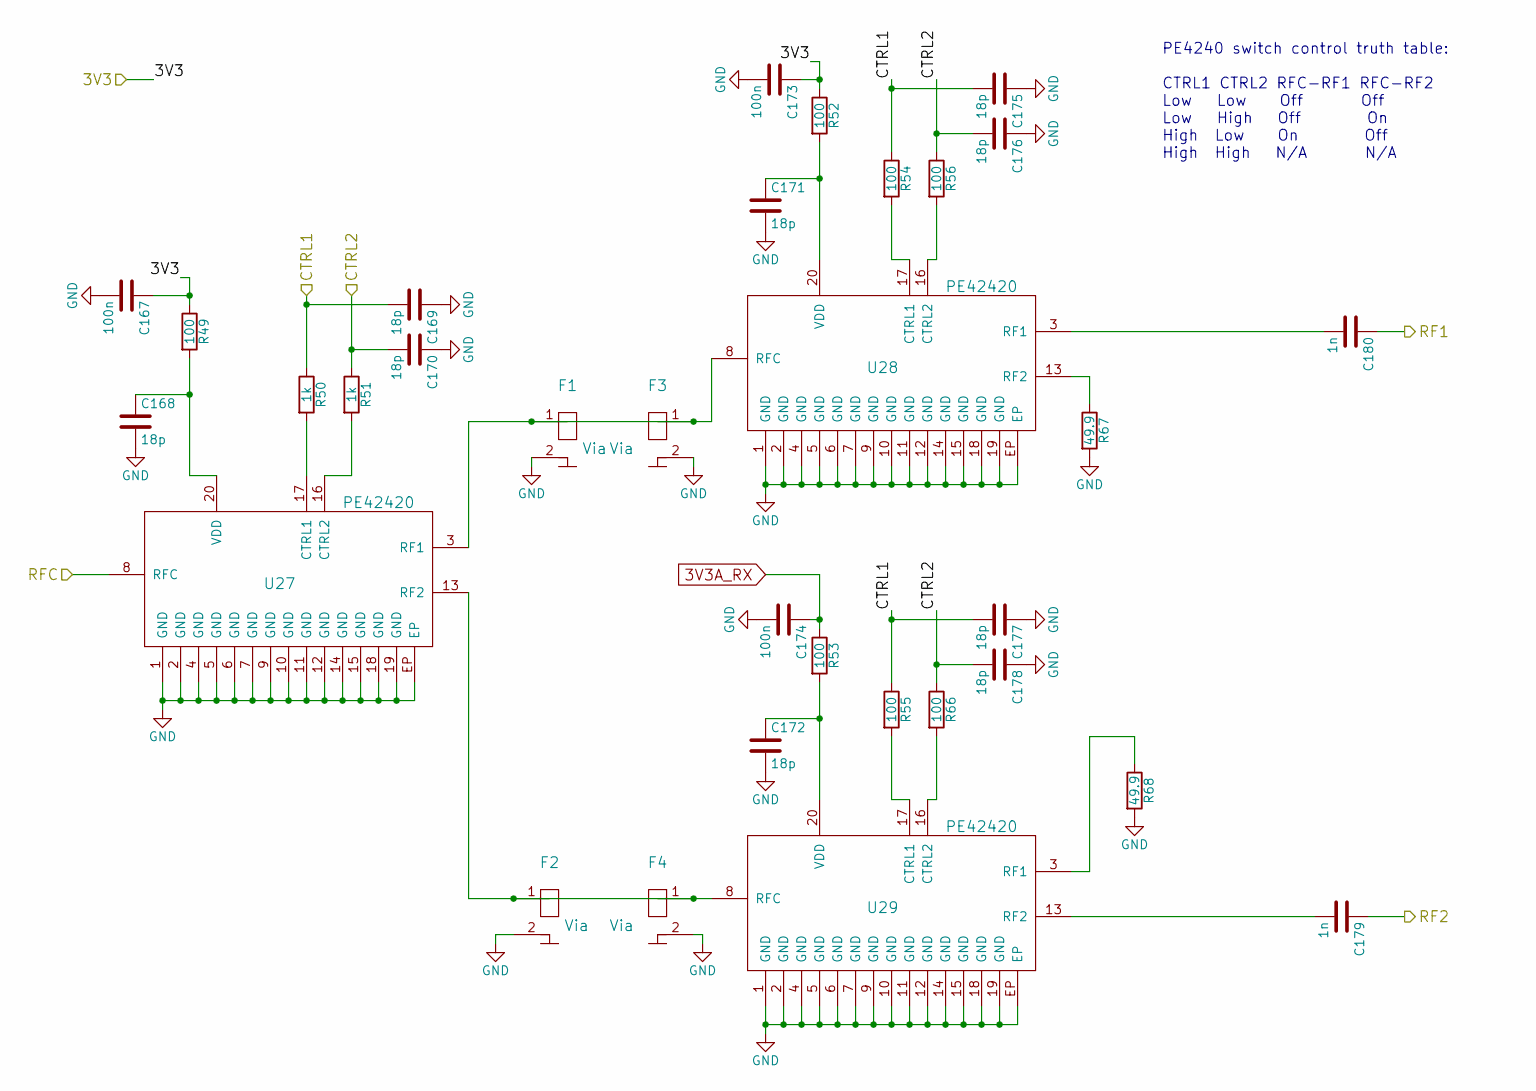
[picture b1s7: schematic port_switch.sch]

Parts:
C167, C173, C174: 100n; C_0402b
C168, C169, C170, C171, C172, C175, C176, C177, C178: 18p; C_0402b
C179, C180: 1n; C_0402b
F1, F2, F3, F4: Via; RF_via
R49, R52, R53, R54, R55, R56, R66: 100; R_0402b
R50, R51: 1k; R_0402b
R67, R68: 49.9; R_0402b
U27, U28, U29: PE42420; TFLGA-20

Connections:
3V3A_RX: C174.1, R53.1; also elsewhere on the board
/3V3A: C167.1, C173.1, R49.1, R52.1; also elsewhere on the board
/PORT1: C180.1; also elsewhere on the board
/PORT2: C179.1; also elsewhere on the board
/PORT_SW0: C169.2, C175.2, C177.2, R50.1, R54.1, R55.1; also elsewhere on the board
/PORT_SW1: C170.2, C176.2, C178.2, R51.1, R56.1, R66.1; also elsewhere on the board
/port switch/RFC: U27.8 (RFC); also elsewhere on the board
GND: C167.2, C168.2, C169.1, C170.1, C171.2, C172.2, C173.2, C174.2, C175.1, C176.1, C177.1, C178.1, F1.2, F2.2, F3.2, F4.2, R67.2, R68.2, U27.1 (GND), U27.2 (GND), U27.4 (GND), U27.5 (GND), U27.6 (GND), U27.7 (GND), U27.9 (GND), U27.10 (GND), U27.11 (GND), U27.12 (GND), U27.14 (GND), U27.15 (GND), U27.18 (GND), U27.19 (GND), U27.EP, U28.1 (GND), U28.2 (GND), U28.4 (GND), U28.5 (GND), U28.6 (GND), U28.7 (GND), U28.9 (GND), U28.10 (GND), U28.11 (GND), U28.12 (GND), U28.14 (GND), U28.15 (GND), U28.18 (GND), U28.19 (GND), U28.EP, U29.1 (GND), U29.2 (GND), U29.4 (GND), U29.5 (GND), U29.6 (GND), U29.7 (GND), U29.9 (GND), U29.10 (GND), U29.11 (GND), U29.12 (GND), U29.14 (GND), U29.15 (GND), U29.18 (GND), U29.19 (GND), U29.EP; also elsewhere on the board
unnamed: C168.1, R49.2, U27.20 (VDD)
unnamed: C171.1, R52.2, U28.20 (VDD)
unnamed: C172.1, R53.2, U29.20 (VDD)
unnamed: C179.2, U29.13 (RF2)
unnamed: C180.2, U28.3 (RF1)
unnamed: F1.1, F3.1, U27.3 (RF1), U28.8 (RFC)
unnamed: F2.1, F4.1, U27.13 (RF2), U29.8 (RFC)
unnamed: R50.2, U27.17 (CTRL1)
unnamed: R51.2, U27.16 (CTRL2)
unnamed: R54.2, U28.17 (CTRL1)
unnamed: R55.2, U29.17 (CTRL1)
unnamed: R56.2, U28.16 (CTRL2)
unnamed: R66.2, U29.16 (CTRL2)
unnamed: R67.1, U28.13 (RF2)
unnamed: R68.1, U29.3 (RF1)

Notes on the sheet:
PE4240 switch control truth table: CTRL1 CTRL2 RFC-RF1 RFC-RF2 Low Low Off Off Low High Off On High Low On Off High High N/A N/A
